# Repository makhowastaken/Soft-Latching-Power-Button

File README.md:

# Soft Latching Power Button
A simple circuit for implementing a momentary power switch

**THIS TESTED AND WORKING**

Update 2023-01-11: I did lots of cleanup in this repository. I made a minor update to the main board file to take advantage of newer kicad features but otherwise it should be unchanged. 

This circuit is intended to replace the power switch in a Game Boy Advance or Game Boy Advance SP but should be usuable in any Game Boy console or other similar device if wired up properly. All labelling is GBA-centric but should be easy enough to translate if you understand what it's doing. The circuit is based around the IRF7317TRPBF – Mosfet Array N and P-Channel chip and should be usuable between 1.5v and 7.5v. Any lower and it will not reliably switch and any higher and it won't switch at all. See [this page from Mosaic Industries](http://www.mosaic-industries.com/embedded-systems/microcontroller-projects/electronic-circuits/push-button-switch-turn-on/switching-battery-power) for more info. 

There is a small quirk with this circuit and I'm not quite sure how to fix it without using a more complex circuit or without wasting power. The Game Boy cannot be restarted as this replacement bypasses the drain resistor installed on the original power switch. The purpose of this resistor is quickly drain all the power from the circuits and fully switch off the GB. Without this resistor, it can take up to 5 seconds for the GB fully switch off, depending on the model and condition. If you try and restart the Game Boy too quickly, it will refuse to power up so it is possible to enter a scenario where the power switch is "on" but the console is "off" and it will not matter how long you wait to try powering it up again, it will not boot unless you switch the MOSFET off again by holding the power switch for 10 seconds or by interrupting power entirely (remove batteries). 

---

SCHEMATIC:

Operation: Press button once to turn on the circuit, press and hold for three seconds to turn the circuit off.

Install: Remove the original power switch. This cannot be installed in parallel. GND pad needs to get soldered to any console ground (or negative battery pad), 2 pad gets soldered to the power input (ideally after the fuse), and C gets soldered to pad C from the GBA power switch (or other power input). Place PCB where there is room and place button where it's accessable and wire the button to GND and SW_C pad on the mod board. See below for button options. [This video covers full assembly and testing.](https://www.youtube.com/watch?v=EvzQTYazzEA)

---

ORDERING THE MAIN BOARD:

BOM:
* Q1: [IRF7317TRPBF](https://www.digikey.com/product-detail/en/infineon-technologies/IRF7317TRPBF/IRF7317PBFCT-ND/812608)
* D1: [MMBD7000LT1G](https://www.digikey.com/product-detail/en/on-semiconductor/MMBD7000LT1G/MMBD7000LT1GOSCT-ND/1139789)
* C1: [0.1uF 0603](https://www.digikey.com/product-detail/en/yageo/CC0603KRX7R6BB104/311-4055-1-ND/8025144)
* C2: [10 uF 0603](https://www.digikey.com/product-detail/en/murata-electronics/GRM188R61A106KE69J/490-14372-1-ND/6606833)
* C3: [1 uF 0603](https://www.digikey.com/product-detail/en/murata-electronics/GRM188R61A105KA61J/490-6408-1-ND/3845605)
* R1: [10K 0603](https://www.digikey.com/product-detail/en/yageo/RC0603FR-0710KL/311-10-0KHRCT-ND/729827)
* R2&R3: [100K 0603](https://www.digikey.com/product-detail/en/susumu/RR0816P-104-D/RR08P100KDCT-ND/432772)
* R4: [300K 0603](https://www.digikey.com/product-detail/en/susumu/RR0816P-304-D/RR08P300KDCT-ND/432783)

Digikey cart [\*.csv](digikey_cart.csv) Note: for the passives (caps, resistors, and diode), there may be better alternatives or even discounts for higher quantities (so ten resistors may literally be cheaper than just three). This cart contains exactly enough parts (except the switch) to build three units.

You need the main board (thinner is better than thicker -- default 1.6mm is fine but thinner or flex allows for tucking it away inside the console more easily)

---

ORDERING THE SWITCH BOARD:

And for a GBA, I have also made two power switch board files. These are to replace the power switch itself on the GAME BOY ADVANCE ONLY. You still need the main board to use with either of these boards. See video link below for a quick demo. 

The rotary style switch board has been tested and does work great but ONLY with "one chip" backlight kits. It will NOT work with funnyplaying backlight kits to control the brightness (they don't like the select button pad being stuck low indefinitely) and it will not work with cloud game store kits either due to the lack of button based controls in their current iterations. [Here is the the switch you need](https://lcsc.com/product-detail/Multi-Directional-Switches_XKB-Connectivity-TM-2023_C318951.html) for this switch board. Board tested working at 1.6mm thickness. Thicker is better than thinner here but thinner boards can work (albeit may have some flex when pressing the button).

The DS Lite style switch board can be made to work with shell cuts but the plastic power switch slider in the housing itself won't line up. I'll keep the board in the repo for now but you have been warned. Can possibly be made to work as a flex PCB with [this momentary switch](https://lcsc.com/product-detail/Slide-Switches_XKB-Connectivity-SK-1391L-2_C319026.html) and then some modifications to the plastic slider (or even a custom slider) but I do not plan to pursue this. 

Otherwise, any SPST switch will work. Very little current is passed through the switch itself (just a few mA and at whatever source voltage you're using) so anything can be made to work. One side goes to ground, the other goes SW-C on the main board.

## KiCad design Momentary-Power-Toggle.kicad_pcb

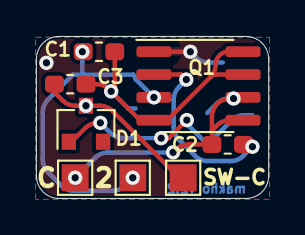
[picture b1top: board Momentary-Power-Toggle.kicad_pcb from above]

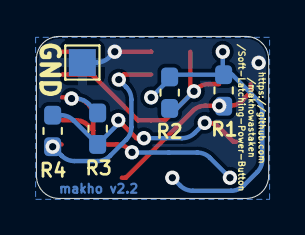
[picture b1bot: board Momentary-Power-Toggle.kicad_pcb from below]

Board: 2 copper layers, 12.9 x 9.0 mm, 13 parts (5 on the bottom side), 7 nets.

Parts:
2: PWR_2; TestPoint_Pad_1.5x1.5mm
C: PWR_C; TestPoint_Pad_1.5x1.5mm
C1: 0.1uF; C_0603_1608Metric_Pad1.05x0.95mm_HandSolder
C2: 10uF; C_0603_1608Metric_Pad1.05x0.95mm_HandSolder
C3: 1uF; C_0603_1608Metric_Pad1.05x0.95mm_HandSolder
D1: MMBD7000LT1G; D_SOT-23_ANK
GND: GND; TestPoint_Pad_1.5x1.5mm
Q1: IRF7317PbF; SOIC-8_3.9x4.9mm_P1.27mm
R1: 10K; R_0603_1608Metric_Pad1.05x0.95mm_HandSolder
R2, R3: 100K; R_0603_1608Metric_Pad1.05x0.95mm_HandSolder
R4: 300K; R_0603_1608Metric_Pad1.05x0.95mm_HandSolder
SW-C: BTN; TestPoint_Pad_1.5x1.5mm

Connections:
D1: C1.1, C3.1, Q1.4, Q1.7, Q1.8, R2.2
GND: GND.1, Q1.1
unnamed: C2.1, Q1.2, R4.2
unnamed: C.1, C2.2, Q1.5, Q1.6, R3.1
unnamed: C3.2, D1.1, R1.2, SW-C.1
unnamed: D1.2, R3.2, R4.1
VCC: 2.1, C1.2, Q1.3, R1.1, R2.1

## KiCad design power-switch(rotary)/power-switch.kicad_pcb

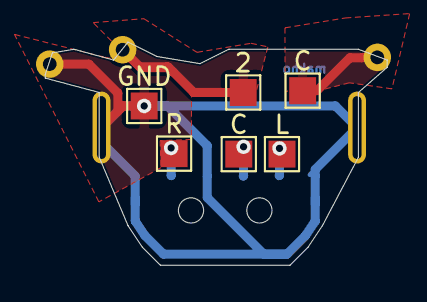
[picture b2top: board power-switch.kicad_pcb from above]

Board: 2 copper layers, 19.0 x 12.4 mm, 8 parts (1 on the bottom side), 3 nets.

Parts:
2: TestPoint_Pad_1.5x1.5mm
C: TestPoint_Pad_1.5x1.5mm
C#2: TestPoint_Pad_1.5x1.5mm
GND: TestPoint_Pad_1.5x1.5mm
L: TestPoint_Pad_1.5x1.5mm
R: TestPoint_Pad_1.5x1.5mm
Ref**: Val**; AGB_Power_Switch2
TM-2023: SW-SMD_TM-2023_v2

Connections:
GND: GND.1, Ref**.3, TM-2023.6, TM-2023.GND, TM-2023.T
VCC: C#2.1, Ref**.1
VDD: 2.1, Ref**.2

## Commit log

2020-08-21 Add files via upload
    fixed schematic error
2020-08-21 updated design rules on PCB
    oshpark preview exposed an error with my design rule settings
2020-08-21 uploaded board renders
2020-08-21 Add files via upload
    updated renders to current version
2020-08-21 Update README.md
    replaced LCSC link with digikey for diode as dual mosfet IC is not available from LCSC
2020-09-06 Update README.md
    fixed a typo and added some notes after testing the mod
2021-08-10 consistify labels
2021-08-10 cleanup
    cleaned up readme, board files, added renders, made small tweaks to some of the boards (added identifiers and changed labels for consistency)
2021-08-10 Update readme.md
    typos
2021-08-10 Update readme.md
    formatting?
2021-08-10 remove spaces from file names
2023-01-12 general cleanup
    defuckulated the repository by removing obsolete board configs, updating schematic image, condensing readmes, etc
2023-01-12 update kicad files (ver 5 -> ver 6)
